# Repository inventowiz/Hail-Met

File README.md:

Hail-Met
========

A repo for work done on the Hail-met project for EECS 473, Fall 2014.

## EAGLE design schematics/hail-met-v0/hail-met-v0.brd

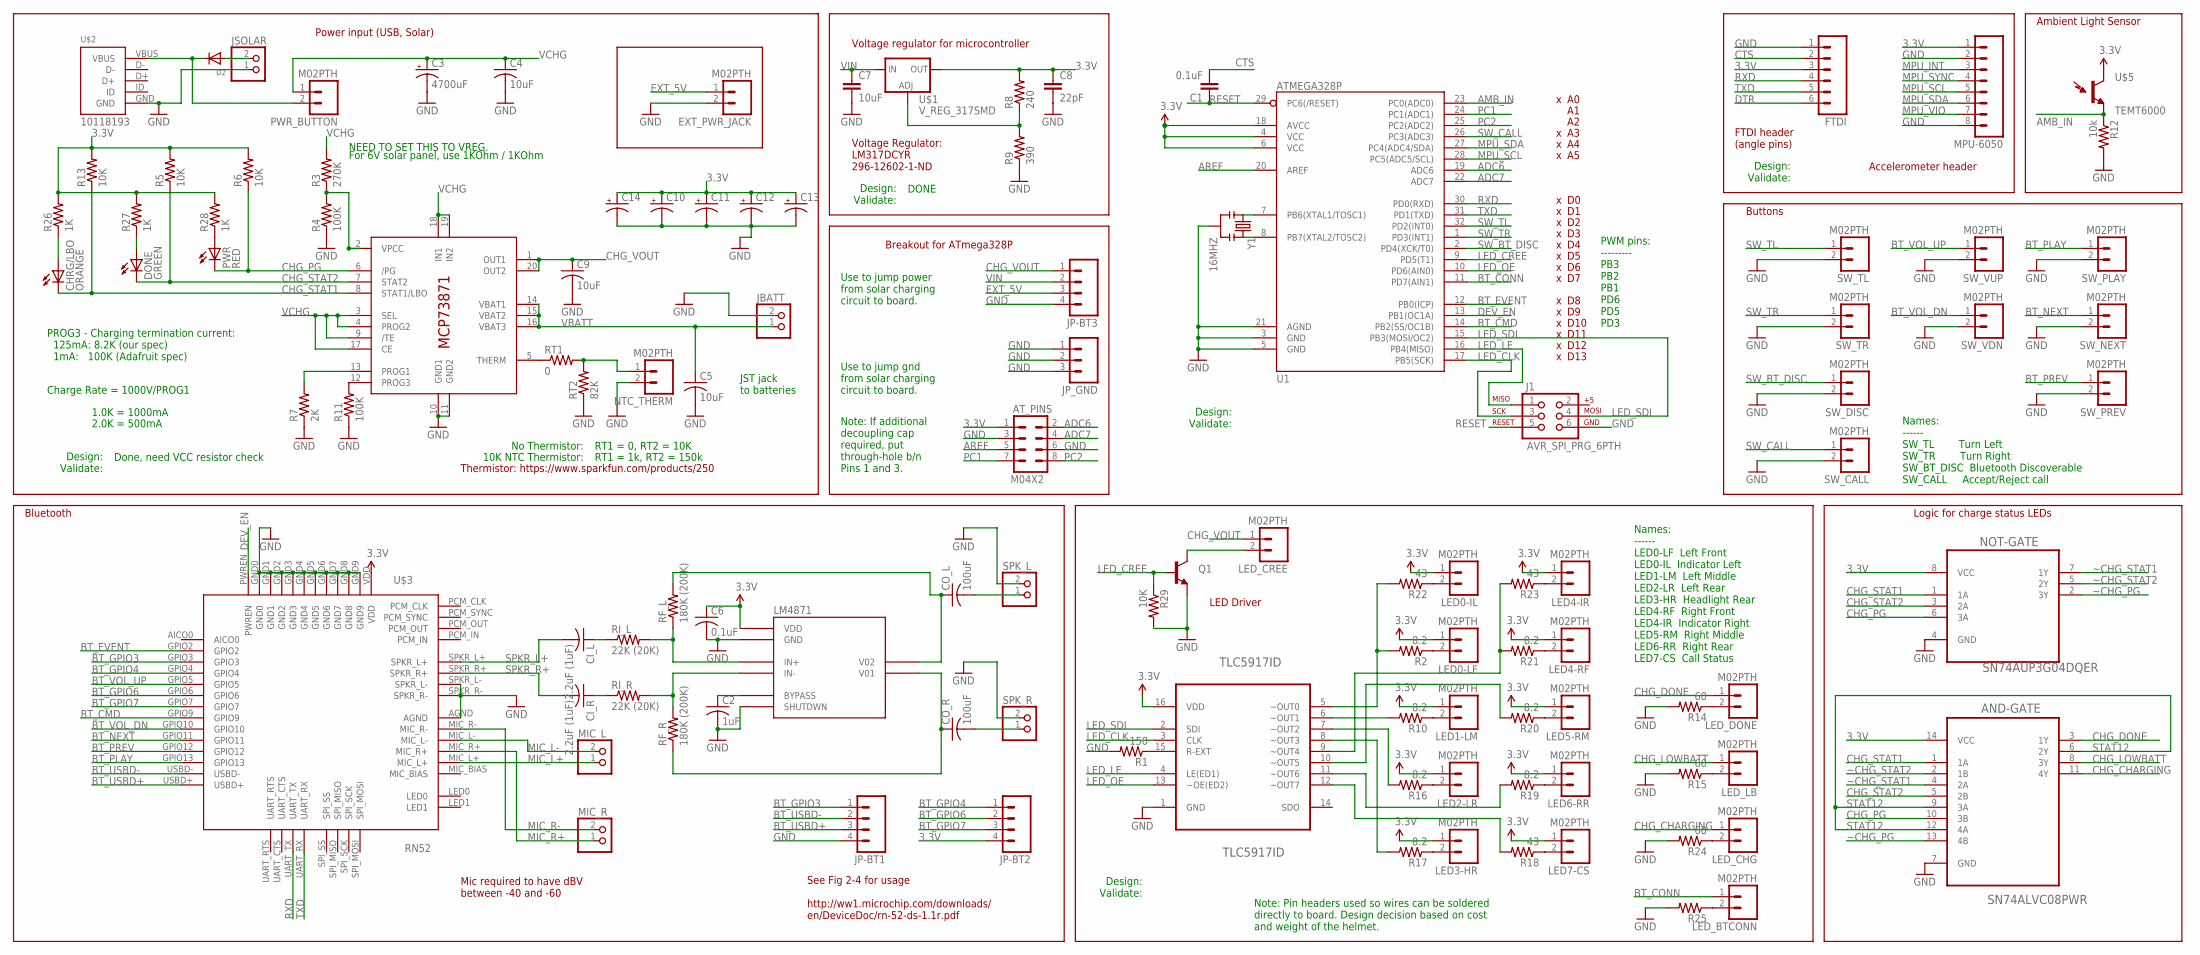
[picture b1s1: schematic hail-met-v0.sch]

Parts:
AND-GATE: SN74ALVC08PWR; SOP65P640X120-14N
AT_PINS: M04X2; 2X4
C1: 0.1uF; 0805
C2: 1uF; C0805K
C3: 4700uF; E5-13
C4, C5, C9: 10uF; C0805K
C6: 0.1uF; C0805K
C7: 10uF; 0805
C8: 22pF; 0805
C10, C11, C12, C13, C14: CAP_POLPTH1; CPOL-RADIAL-100UF-25V
CHRG/LBO: ORANGE; CHIP-LED0805
CI_L: 2.2uF (1uF); C0805K
CI_R: 2.2uF (1uF); C0805K
CO_L: 100uF; C0805K
CO_R: 100uF; C0805K
D2: DIODESOD-123; SOD-123
DONE: GREEN; CHIP-LED0805
EXT_PWR_JACK: M02PTH; 1X02
FTDI: M06LOCK; 1X06_LOCK
IC1: MCP73871; QFN20
J1: AVR_SPI_PRG_6PTH; 2X3
JBATT: JST_2PIN-SMT; JST-PH-2-SMT
JP-BT1, JP-BT2, JP-BT3: M04LOCK; 1X04_LOCK
JP_GND: M03LOCK; 1X03_LOCK
JSOLAR: JST_2PIN-SMT; JST-PH-2-SMT
LED0-IL, LED0-LF, LED1-LM, LED2-LR, LED3-HR, LED4-IR, LED4-RF, LED5-RM, LED6-RR, LED7-CS: M02PTH; 1X02
LED_BTCONN: M02PTH; 1X02
LED_CHG: M02PTH; 1X02
LED_CREE: M02PTH; 1X02
LED_DONE: M02PTH; 1X02
LED_LB: M02PTH; 1X02
LM4871: LM4871; SO08
MIC_L: JST_2PIN-SMT; JST-PH-2-SMT
MIC_R: JST_2PIN-SMT; JST-PH-2-SMT
MPU-6050: M08LOCK; 1X08_LOCK
NOT-GATE: SN74AUP3G04DQER; SON35P100X140X40-8N
NTC_THERM: M02PTH; 1X02
PWR: RED; CHIP-LED0805
PWR_BUTTON: M02PTH; 1X02
Q1: TRANSISTOR_NPNSOT23-3; SOT23-3
R1: 150; 0805
R2, R10, R16, R17, R19, R20, R21: 8.2; 0805
R3: 270K; 0805
R4, R11: 100K; 0805
R5, R6, R13, R29: 10K; 0805
R7: 2K; 0805
R8: 240; 0805
R9: 390; 0805
R12: 10k; 0805
R14, R15, R24: 60; 0805
R18, R22, R23: 43; 0805
R25: RESISTOR0805-RES; 0805
R26, R27, R28: 1K; 0805
RF_L: 180K (200K); 0805
RF_R: 180K (200K); 0805
RI_L: 22K (20K); 0805
RI_R: 22K (20K); 0805
RT1: 0; 0805
RT2: 82K; 0805
SPK_L: JST_2PIN-SMT; JST-PH-2-SMT
SPK_R: JST_2PIN-SMT; JST-PH-2-SMT
SW_CALL: M02PTH; 1X02
SW_DISC: M02PTH; 1X02
SW_NEXT: M02PTH; 1X02
SW_PLAY: M02PTH; 1X02
SW_PREV: M02PTH; 1X02
SW_TL: M02PTH; 1X02
SW_TR: M02PTH; 1X02
SW_VDN: M02PTH; 1X02
SW_VUP: M02PTH; 1X02
TLC5917ID: TLC5917ID; SOIC127P600X175-16N
U1: ATMEGA328P; TQFP32-08
U$1: V_REG_317SMD; SOT223
U$2: 10118193
U$3: RN52
U$5: TEMT6000; TEMT6000-SEN
Y1: 16MHZ; RESONATOR-SMD

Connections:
3.3V: AND-GATE.14 (VCC), AT_PINS.1, C6.1, C8.1, C10.1 (+), C11.1 (+), C12.1 (+), C13.1 (+), C14.1 (+), FTDI.3, JP-BT2.4, LED0-IL.1, LED0-LF.1, LED1-LM.1, LED2-LR.1, LED3-HR.1, LED4-IR.1, LED4-RF.1, LED5-RM.1, LED6-RR.1, LED7-CS.1, LM4871.6 (VDD), MPU-6050.1, NOT-GATE.8 (VCC), R5.2, R6.2, R8.2, R13.2, R26.2, R27.2, R28.2, TLC5917ID.16 (VDD), U1.4 (VCC), U1.6 (VCC), U1.18 (AVCC), U$1.2 (OUT), U$3.VDD, U$5.COLLECTOR (C1)
ADC6: AT_PINS.2, U1.19 (ADC6)
ADC7: AT_PINS.4, U1.22 (ADC7)
AMB_IN: R12.1, U1.23 (PC0(ADC0)), U$5.EMITTER (E1)
AREF: AT_PINS.5, U1.20 (AREF)
BT_CMD: U1.14 (PB2(SS/OC1B)), U$3.GPIO9
BT_CONN: LED_BTCONN.1, U1.11 (PD7(AIN1))
BT_EVENT: U1.12 (PB0(ICP)), U$3.GPIO2
BT_GPIO3: JP-BT1.1, U$3.GPIO3
BT_GPIO4: JP-BT2.1, U$3.GPIO4
BT_GPIO6: JP-BT2.2, U$3.GPIO6
BT_GPIO7: JP-BT2.3, U$3.GPIO7
BT_NEXT: SW_NEXT.1, U$3.GPIO11
BT_PLAY: SW_PLAY.1, U$3.GPIO13
BT_PREV: SW_PREV.1, U$3.GPIO12
BT_USBD+: JP-BT1.3, U$3.USBD+
BT_USBD-: JP-BT1.2, U$3.USBD-
BT_VOL_DN: SW_VDN.1, U$3.GPIO10
BT_VOL_UP: SW_VUP.1, U$3.GPIO5
CHG_CHARGING: AND-GATE.11 (4Y), LED_CHG.1
CHG_DONE: AND-GATE.3 (1Y), LED_DONE.1
CHG_LOWBATT: AND-GATE.8 (3Y), LED_LB.1
CHG_PG: AND-GATE.10 (3B), IC1.6 (/PG), NOT-GATE.6 (3A), PWR.C, R6.1
CHG_STAT1: AND-GATE.1 (1A), CHRG/LBO.C, IC1.8 (STAT1/LBO), NOT-GATE.1 (1A), R13.1
CHG_STAT2: AND-GATE.5 (2B), DONE.C, IC1.7 (STAT2), NOT-GATE.3 (2A), R5.1
CHG_VOUT: C9.1, IC1.1 (OUT1), IC1.20 (OUT2), JP-BT3.1, LED_CREE.1
CTS: C1.2, FTDI.2
DEV_EN: U1.13 (PB1(OC1A)), U$3.PWREN
DTR: FTDI.6
EXT_5V: EXT_PWR_JACK.1, JP-BT3.3
GND: AND-GATE.7 (GND), AT_PINS.3, AT_PINS.6, C2.2, C3.-, C4.2, C5.2, C6.2, C7.2, C8.2, C9.2, C10.2 (-), C11.2 (-), C12.2 (-), C13.2 (-), C14.2 (-), EXT_PWR_JACK.2, FTDI.1, IC1.10 (GND1), IC1.11 (GND2), J1.6, JBATT.2 (1), JP-BT1.4, JP-BT3.4, JP_GND.1, JP_GND.2, JP_GND.3, JSOLAR.1 (2), LM4871.1 (SHUTDWN), LM4871.7 (GND), MPU-6050.2, MPU-6050.8, NOT-GATE.4 (GND), NTC_THERM.2, Q1.2 (E), R1.2, R4.1, R7.1, R9.1, R11.1, R12.2, R14.2, R15.2, R24.2, R25.2, R29.2, RT2.1, SPK_L.2 (1), SPK_R.2 (1), SW_CALL.2, SW_DISC.2, SW_NEXT.2, SW_PLAY.2, SW_PREV.2, SW_TL.2, SW_TR.2, SW_VDN.2, SW_VUP.2, TLC5917ID.1 (GND), U1.3 (GND), U1.5 (GND), U1.21 (AGND), U$2.GND, U$3.AGND, U$3.GND0, U$3.GND1, U$3.GND2, U$3.GND3, U$3.GND4, U$3.GND5, U$3.GND6, U$3.GND7, U$3.GND8, U$3.GND9, U$3.SPKR_L-, U$3.SPKR_R-, Y1.2
LED_CLK: J1.3, TLC5917ID.3 (CLK), U1.17 (PB5(SCK))
LED_CREE: Q1.1 (B), R29.1, U1.9 (PD5(T1))
LED_LE: J1.1, TLC5917ID.4 (LE(ED1)), U1.16 (PB4(MISO))
LED_OE: TLC5917ID.13 (~OE(ED2)), U1.10 (PD6(AIN0))
LED_SDI: J1.4, TLC5917ID.2 (SDI), U1.15 (PB3(MOSI/OC2))
MIC_L+: MIC_L.1 (2), U$3.MIC_L+
MIC_L-: MIC_L.2 (1), U$3.MIC_L-
MIC_R+: MIC_R.1 (2), U$3.MIC_R+
MIC_R-: MIC_R.2 (1), U$3.MIC_R-
MPU_INT: MPU-6050.3
MPU_SCL: MPU-6050.5, U1.28 (PC5(ADC5/SCL))
MPU_SDA: MPU-6050.6, U1.27 (PC4(ADC4/SDA))
MPU_SYNC: MPU-6050.4
MPU_VIO: MPU-6050.7
unnamed: U1.7 (PB6(XTAL1/TOSC1)), Y1.1
unnamed: U1.8 (PB7(XTAL2/TOSC2)), Y1.3
unnamed: IC1.5 (THERM), RT1.1
unnamed: R8.1, R9.2, U$1.1 (ADJ)
unnamed: R2.2, R22.2, TLC5917ID.5 (~OUT0)
unnamed: R10.2, TLC5917ID.6 (~OUT1)
unnamed: R16.2, TLC5917ID.7 (~OUT2)
unnamed: R17.2, TLC5917ID.8 (~OUT3)
unnamed: R21.2, R23.2, TLC5917ID.9 (~OUT4)
unnamed: R20.2, TLC5917ID.10 (~OUT5)
unnamed: R19.2, TLC5917ID.11 (~OUT6)
unnamed: R18.2, TLC5917ID.12 (~OUT7)
unnamed: NTC_THERM.1, RT1.2, RT2.2
unnamed: CO_L.2, SPK_L.1 (2)
unnamed: D2.A, JSOLAR.2 (1)
unnamed: LED_BTCONN.2, R25.1
unnamed: IC1.2 (VPCC), R3.1, R4.2
unnamed: IC1.12 (PROG3), R11.2
unnamed: LED_CREE.2, Q1.3 (C)
unnamed: CHRG/LBO.A, R26.1
unnamed: DONE.A, R27.1
unnamed: LED_DONE.2, R14.1
unnamed: PWR.A, R28.1
unnamed: LED_LB.2, R15.1
unnamed: CO_R.2, SPK_R.1 (2)
unnamed: LED_CHG.2, R24.1
unnamed: R1.1, TLC5917ID.15 (R-EXT)
unnamed: LED0-LF.2, R2.1
unnamed: LED4-RF.2, R21.1
unnamed: LED5-RM.2, R20.1
unnamed: LED6-RR.2, R19.1
unnamed: LED7-CS.2, R18.1
unnamed: LED3-HR.2, R17.1
unnamed: LED1-LM.2, R10.1
unnamed: LED2-LR.2, R16.1
unnamed: LED0-IL.2, R22.1
unnamed: LED4-IR.2, R23.1
unnamed: LM4871.4 (IN-), RF_R.2, RI_R.2
unnamed: CI_L.1, RI_L.1
unnamed: C2.1, LM4871.2 (BYPASS)
unnamed: LM4871.3 (IN+), RF_L.1, RI_L.2
unnamed: CI_R.1, RI_R.1
unnamed: D2.C, PWR_BUTTON.2, U$2.VBUS
PC1: AT_PINS.7, U1.24 (PC1(ADC1))
PC2: AT_PINS.8, U1.25 (PC2(ADC2))
PROG1: IC1.13 (PROG1), R7.2
RESET: C1.1, J1.5, U1.29 (PC6(/RESET))
RXD: FTDI.4, U1.30 (PD0(RXD)), U$3.UART_TX
SPKR_L: CO_L.1, LM4871.8 (V02), RF_L.2
SPKR_L+: CI_L.2, U$3.SPKR_L+
SPKR_R: CO_R.1, LM4871.5 (V01), RF_R.1
SPKR_R+: CI_R.2, U$3.SPKR_R+
STAT12: AND-GATE.6 (2Y), AND-GATE.9 (3A), AND-GATE.12 (4A)
SW_BT_DISC: SW_DISC.1, U1.2 (PD4(XCK/T0))
SW_CALL: SW_CALL.1, U1.26 (PC3(ADC3))
SW_TL: SW_TL.1, U1.32 (PD2(INT0))
SW_TR: SW_TR.1, U1.1 (PD3(INT1))
TXD: FTDI.5, U1.31 (PD1(TXD)), U$3.UART_RX
VBATT: C5.1, IC1.14 (VBAT1), IC1.15 (VBAT2), IC1.16 (VBAT3), JBATT.1 (2)
VCHG: C3.+, C4.1, IC1.3 (SEL), IC1.4 (PROG2), IC1.9 (/TE), IC1.17 (CE), IC1.18 (IN1), IC1.19 (IN2), PWR_BUTTON.1, R3.2
VIN: C7.1, JP-BT3.2, U$1.3 (IN)
~CHG_PG: AND-GATE.13 (4B), NOT-GATE.2 (3Y)
~CHG_STAT1: AND-GATE.4 (2A), NOT-GATE.7 (1Y)
~CHG_STAT2: AND-GATE.2 (1B), NOT-GATE.5 (2Y)

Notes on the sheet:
PWM pins: --------- PB3 PB2 PB1 PD6 PD5 PD3
JST jack to batteries
Voltage regulator for microcontroller
LED Driver
Power input (USB, Solar)
No Thermistor:
10K NTC Thermistor:
RT1 = 0, RT2 = 10K
RT1 = 1k, RT2 = 150k
Charge Rate = 1000V/PROG1
1.0K = 1000mA
2.0K = 500mA
NEED TO SET THIS TO VREG. For 6V solar panel, use 1KOhm / 1KOhm
DONE
Design: Validate:
Done, need VCC resistor check
Bluetooth
Note: Pin headers used so wires can be soldered directly to board. Design decision based on cost and weight of the helmet.
Names: ------ LED0-LF Left Front LED0-IL Indicator Left LED1-LM Left Middle LED2-LR Left Rear LED3-HR Headlight Rear LED4-RF Right Front LED4-IR Indicator Right LED5-RM Right Middle LED6-RR Right Rear LED7-CS Call Status
Thermistor: https://www.sparkfun.com/products/250
Accelerometer header
FTDI header (angle pins)
Ambient Light Sensor
Buttons
Names: ------ SW_TL Turn Left SW_TR Turn Right SW_BT_DISC Bluetooth Discoverable SW_CALL Accept/Reject call
Voltage Regulator: LM317DCYR 296-12602-1-ND
Mic required to have dBV between -40 and -60
D10
D11
D12
See Fig 2-4 for usage http://ww1.microchip.com/downloads/ en/DeviceDoc/rn-52-ds-1.1r.pdf
D13
Logic for charge status LEDs
Breakout for ATmega328P
Note: If additional decoupling cap required, put through-hole b/n Pins 1 and 3.
Use to jump gnd from solar charging circuit to board.
Use to jump power from solar charging circuit to board.
PROG3 - Charging termination current: 125mA: 8.2K (our spec) 1mA: 100K (Adafruit spec)

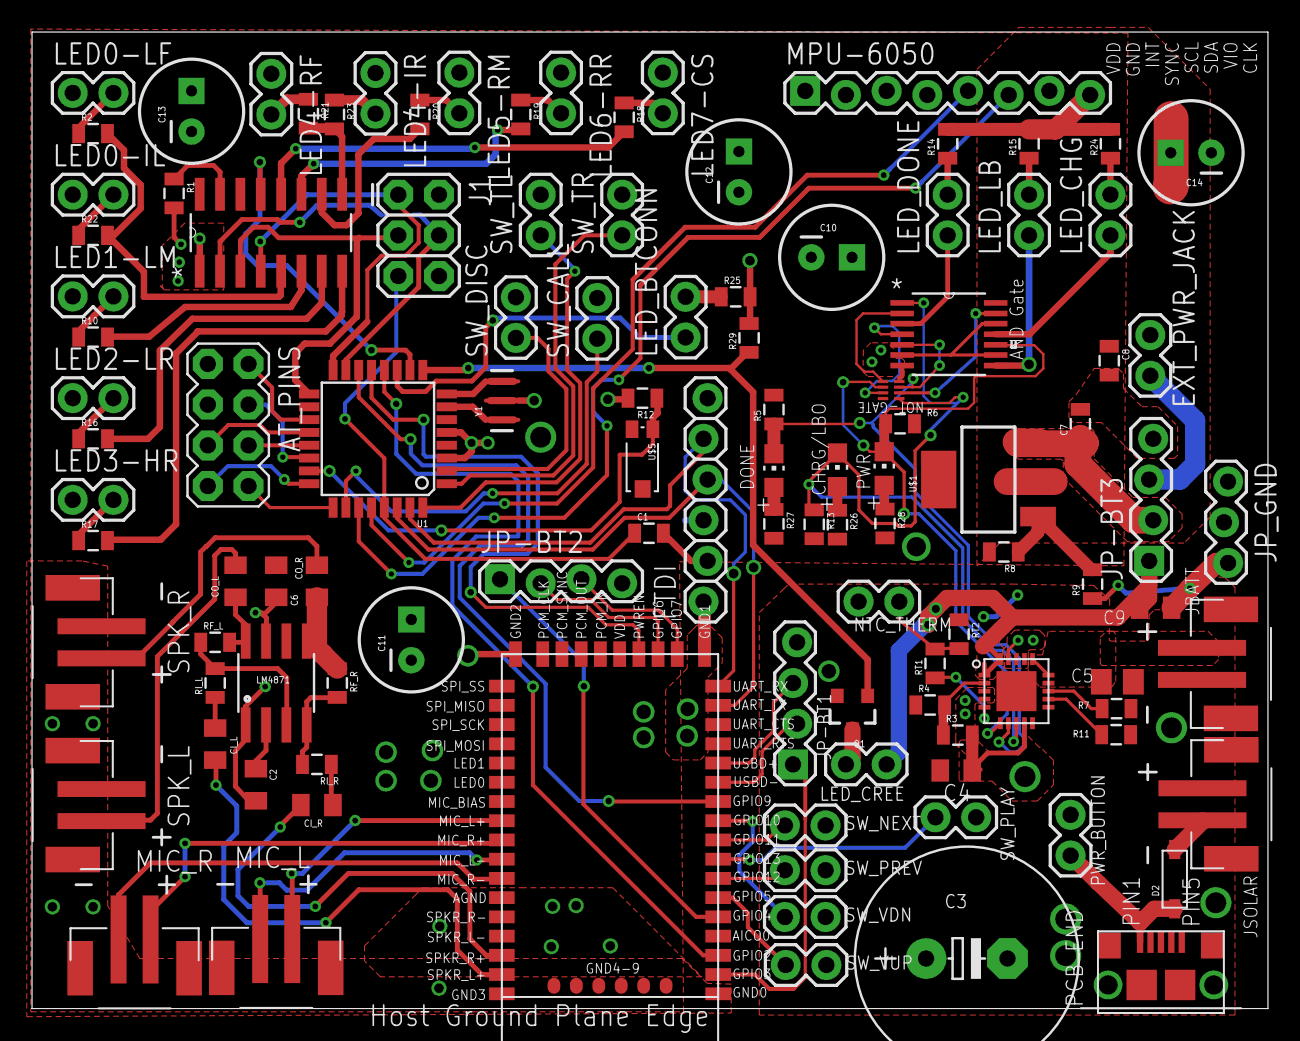
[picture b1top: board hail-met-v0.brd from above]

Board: 2 copper layers, 77.1 x 61.0 mm, 110 parts (0 on the bottom side), 105 nets.

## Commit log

2014-10-05 wrote initial LED driver library
2014-10-05 added LED driver spec sheet
2014-10-09 Started PCB schematic
2014-10-10 updated schematic, added datasheets
2014-10-10 cleaned up EAGLE temp files
2014-10-14 Added Bluetooth libraries and Arduino sketch
2014-10-15 Changed LED Driver code to work on HW SPI instead of bit-bang
2014-10-15 Moved all libraries into a multi-file sketch. This should make managing the code easier
2014-10-15 updated schematic
2014-10-17 Cleaned up the sketch
2014-10-17 worked on schematic
2014-10-17 Added libraries to sketch
2014-10-17 compileable. moved libraries
2014-10-18 Added some light sensing code
2014-10-23 Added bluetooth pairing button
2014-10-23 updated schematic with pins (CPU pins not verified)
2014-10-24 modified schematic slightly and began board layout.
2014-10-24 updated schematic/board and datasheets
2014-10-26 Added 3d models
2014-10-26 whoops, fixed the mistake hopefully
2014-10-27 finished initial schematic and routing, updated software pin assignment
2014-10-27 added some power planes
2014-10-27 routing pcb
2014-10-28 added to layout
2014-10-28 updated routing
2014-10-29 worked on routing
2014-10-30 finished initial PCB routing/layout
2014-10-30 Added more 3d designs
2014-10-30 added headlight code (NEED TEST) and updated pcb
2014-10-30 Fixed an error with compilation, but it works now
2014-10-31 added pull-down for transistor
2014-10-31 added some decoupling caps to the board, prep for ben
2014-10-31 finalized board design, added new npn datasheet
2014-11-01 ordered pcb
2014-11-03 added in functionality to accept or decline calls over bluetooth with a button
2014-11-04 Added more 3d ish
2014-11-04 added stencils, BOM, and finalized PCB
2014-11-04 changed some cube files, modified the helmet brim
2014-11-05 added order
2014-11-13 Refactored button code, fixed bugs, cleaned up main function, and added voice command capability
2014-11-17 Cleaned up code and added hang up functionality
2014-11-17 +call indicator leds, fixed rn52 state reading/polling
2014-11-17 Added more 3d models woo
2014-11-17 +Programming mode, no need to disconnect RX/TX lines to reprogram arduino. Simply press and hold discovery button
2014-11-17 Changed pins to reflect PCB
2014-11-17 +Better headlight enable/disable and variable brightness
2014-11-19 Made it so only one turn signal can be on at a time
2014-11-20 Started v1 of board
2014-11-21 updated schematics (v0, v1) and datasheets
2014-11-22 updated schematic with charge termination current resistor
2014-11-24 Added chinstrap module version with spots for screws
2014-11-24 updated and routed v1 board
2014-11-24 added updated oscillator library
2014-11-24 Added front led signals
2014-11-24 Added solar panel housings
2014-11-24 updated board v1
2014-11-25 finished all 3d designs I think
2014-11-27 modified board with audio amp values
2014-12-01 added poster design beginnings
2014-12-01 updated schematic with new LED driver values
2014-12-02 Added low battery indicator on call led
2014-12-03 Added startup config
2014-12-03 Added poster work
2014-12-03 Added final 3d parts
2014-12-03 Changed light sensor pin
2014-12-03 Taillight now comes on with headlight and blinks, lowered speaker gain
2014-12-06 Code update for design expo. Lowered CREE brightness, added BT init

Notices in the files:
parts and their libraries:
SparkFun-Passives: Licensing: Creative Commons ShareAlike 4.0 International - https://creativecommons.org/licenses/by-sa/4.0
SparkFun-Capacitors: Licensing: CC v3.0 Share-Alike You are welcome to use this library for commercial purposes.
